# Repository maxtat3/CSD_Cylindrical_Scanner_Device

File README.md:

# Cylindrical Scanner Device (CSD)
This electronic-mechanical device for research of processes in the activation of surfaces by diffusion welding and soldering cylinder samples in a vacuum. It is used for scientific research.
Named: Cylindrical Scanner Device (CSD) or Surface Activation Scanner (SAC) .
You can [view photo](https://drive.google.com/folderview?id=0B9YGrJoTVMatWHJlU2hkQTU4MW8&usp=sharing) when debug this device.

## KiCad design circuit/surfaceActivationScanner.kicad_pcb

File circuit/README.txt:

Project name: 
определение осаждения окиси хрома в вакууме
determining the deposition of chromium oxide in vacuum

This project create in old stable kicad version jul 2013.

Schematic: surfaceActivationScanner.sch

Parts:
C1: 100uF 16V; CP_EIA-7343-31_Kemet-D
C2: 470uF 16V; CP_Elec_10x10
C3: 100uF 6.3V; CP_EIA-3528-21_Kemet-B
C4, C5, C6, C7, C8, C10, C11, C12, C15, C16, C19, C21, C23: 100nF; C_0805_2012Metric
C9, C13, C14: 10uF 16V; CP_EIA-3528-21_Kemet-B
C17, C18: 22pF; C_0805_2012Metric
C20: 1uF; C_1210_3225Metric
C22: 22uF 6.3V; CP_EIA-3528-21_Kemet-B
D1: 10MQ040N; D_SMA
D2: Power; LED_0805_2012Metric
D3: LL4148; D_MiniMELF
D4: FT232_TX_LED; LED_0805_2012Metric
D5: FT232_RX_LED; LED_0805_2012Metric
J1: Conn_power; JST_EH_B02B-EH-A_1x02_P2.50mm_Vertical
J2: Conn_sensor_led; JST_EH_B02B-EH-A_1x02_P2.50mm_Vertical
J3: Conn_opto_int; JST_EH_B03B-EH-A_1x03_P2.50mm_Vertical
J4: Conn_sensor_VT; JST_EH_B02B-EH-A_1x02_P2.50mm_Vertical
J5: Conn btn start/stop msr; JST_EH_B02B-EH-A_1x02_P2.50mm_Vertical
J6: Conn led start/stop msr; JST_EH_B02B-EH-A_1x02_P2.50mm_Vertical
J7: Conn_USB; JST_EH_B03B-EH-A_1x03_P2.50mm_Vertical
J8: AVR-ISP-6; IDC-Header_2x03_P2.54mm_Vertical
JP1: select; JST_EH_B03B-EH-A_1x03_P2.50mm_Vertical
JP2: sel ADC; JST_EH_B03B-EH-A_1x03_P2.50mm_Vertical
L1: 100uH; L_Radial_D8.7mm_P5.00mm_Fastron_07HCP
L2, L3: 100uH; L_Vishay_IHLP-1616
R1, R8, R10, R11, R12, R13: 1k; R_0805_2012Metric
R2, R3, R4, R6, R7: 10k; R_0805_2012Metric
R5, R9: 510E; R_0805_2012Metric
RV1: 1k; Potentiometer_Vishay_T7-YA_Single_Vertical
RV2, RV3: 1k; Potentiometer_Bourns_3296W_Vertical
RV4: 33k; Potentiometer_Bourns_3296W_Vertical
U1: AP1117-50; SOT-223-3_TabPin2
U2: MCP3421A0T-ECH; SOT-23-6_Handsoldering
U3: ATmega8-16AU; TQFP-32_7x7mm_P0.8mm
U4: LM324; SOIC-14_3.9x8.7mm_P1.27mm
U5: FT232RL; SSOP-28_5.3x10.2mm_P0.65mm
Y1: 7.3728 MHz; Crystal_HC49-U_Vertical

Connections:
+9V: C1.1, C4.1, D1.1, L1.1; also elsewhere on the board
/adc_scl: R4.2, U2.3 (SCL), U3.28 (PC5)
/adc_sda: R3.2, U2.4 (SDA), U3.27 (PC4)
/btnStartStop: J5.1, R7.2, U3.32 (PD2)
/ledStartStop: R9.2, U3.13 (PB1)
/mcu_RX: R10.1, U3.30 (PD0)
/mcu_TX: R11.1, U3.31 (PD1)
/miso: J8.1, U3.16 (PB4)
/mosi: J8.4, U3.15 (PB3)
/optoInt: J3.3, R6.2, U3.12 (PB0)
/sck: J8.3, U3.17 (PB5)
/sensor: JP2.3, U3.23 (PC0)
/smen: U3.1 (PD3); also elsewhere on the board
/smw1: U3.2 (PD4); also elsewhere on the board
/smw2: U3.9 (PD5); also elsewhere on the board
/smw3: U3.10 (PD6); also elsewhere on the board
/smw4: U3.11 (PD7); also elsewhere on the board
/~reset: C11.1, D3.2, J8.5, R2.2, U3.29 (PC6/~RESET)
GND: C1.2, C2.2, C3.2, C4.2, C5.2, C6.2, C7.2, C8.2, C9.2, C10.2, C11.2, C12.2, C13.2, C14.2, C15.2, C16.1, C17.2, C18.2, C19.2, C20.2, C21.2, C22.2, C23.2, D2.1 (A), J1.2, J2.2, J3.2, J5.2, J6.2, J7.3, J8.6, R8.2, RV3.2, RV3.3, U1.1 (GND), U2.2 (Vss), U2.6 (Vin-), U3.3 (GND), U3.5 (GND), U3.21 (AGND), U4.11 (V-), U5.7, U5.18, U5.21, U5.25, U5.26; also elsewhere on the board
unnamed: C2.1, C5.1, L1.2, U1.3 (VI)
unnamed: C12.1, C13.1, L2.1, U3.18 (AVCC)
unnamed: C17.1, U3.7 (PB6/XTAL1), Y1.2
unnamed: C18.1, U3.8 (PB7/XTAL2), Y1.1
unnamed: C19.1, U3.20 (AREF)
unnamed: C20.1, JP1.2, U4.3 (+)
unnamed: C21.1, C22.1, L3.1, U5.4, U5.20
unnamed: C23.1, U5.17
unnamed: D1.2, J1.1
unnamed: D2.2 (K), R1.1
unnamed: D4.1 (A), U5.23
unnamed: D4.2 (K), R12.2
unnamed: D5.1 (A), U5.22
unnamed: D5.2 (K), R13.2
unnamed: J2.1, RV1.1
unnamed: J3.1, R5.1
unnamed: J4.1, JP1.3, RV2.2, RV2.3
unnamed: J4.2, JP1.1, RV3.1
unnamed: J6.1, R9.1
unnamed: J7.1, U5.15
unnamed: J7.2, U5.16
unnamed: JP2.1, U2.1 (Vin+)
unnamed: JP2.2, RV4.2, RV4.3, U4.7
unnamed: R8.1, RV4.1, U4.6 (-)
unnamed: R10.2, U5.1
unnamed: R11.2, U5.5
unnamed: U4.1, U4.2 (-), U4.5 (+)

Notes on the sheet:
mcu_RX_green_led
mcu_TX_orange_led
ft232 TX -> mcu RX
ft232 RX <- mcu TX
Sensor LED current set
100nF вместо 0805 в свойствах артикулы для 0603.
Connected to opto interrupter. This help step motor determine start position. Pinout description: 1 - led vcc power 2 - gnd 3 - out opto transistor signal

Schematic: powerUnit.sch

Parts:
C24, C27, C29, C30: 100nF; C_0805_2012Metric
C25: 470uF 16V; CP_Elec_10x12.5
C26: 68uF 16V; CP_EIA-3528-21_Kemet-B
C28: 22uF 16V; CP_EIA-3528-21_Kemet-B
C31: 220pF; C_0805_2012Metric
D6, D7, D8, D9: US1M; D_SMA
D10: 10MQ040N; D_SMA
L4: 15uH; L_12x12mm_H6mm
M1: Stepper_Motor_unipolar_5pin; JST_EH_B05B-EH-A_1x05_P2.50mm_Vertical
Q1, Q2, Q3, Q4: IRLML0030; SOT-23
R14, R16, R19, R23, R25: 1k; R_0805_2012Metric
R15, R21, R24, R26: 51k; R_0805_2012Metric
R17: 22k; R_0805_2012Metric
R18, R22: 100k; R_0805_2012Metric
R20: 68k; R_0805_2012Metric
RV5: 1k; Potentiometer_Vishay_T7-YA_Single_Vertical
U6: MP1584EN-LF-Z; SOIC-8-1EP_3.9x4.9mm_P1.27mm_EP2.35x2.35mm

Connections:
+9V: C26.1, C27.1, U6.7; also elsewhere on the board
/smen: R16.1; also elsewhere on the board
/smw1: R14.2; also elsewhere on the board
/smw2: R19.2; also elsewhere on the board
/smw3: R23.2; also elsewhere on the board
/smw4: R25.2; also elsewhere on the board
GND: C24.2, C25.2, C26.2, C27.2, C28.2, C29.2, C31.2, D10.2, Q1.2, Q2.2, Q3.2, Q4.2, R15.1, R17.2, R18.2, R21.1, R22.2, R24.1, R26.1, U6.5; also elsewhere on the board
unnamed: C24.1, C25.1, C28.1, C29.1, D6.1, D7.1, D8.1, D9.1, L4.2, M1.1, RV5.3
unnamed: C30.1, U6.8
unnamed: C30.2, D10.1, L4.1, U6.1
unnamed: C31.1, R20.2
unnamed: D6.2, M1.5, Q4.3
unnamed: D7.2, M1.4, Q3.3
unnamed: D8.2, M1.2, Q2.3
unnamed: D9.2, M1.3, Q1.3
unnamed: Q1.1, R14.1, R15.2
unnamed: Q2.1, R19.1, R21.2
unnamed: Q3.1, R23.1, R24.2
unnamed: Q4.1, R25.1, R26.2
unnamed: R16.2, R17.1, U6.2
unnamed: R18.1, U6.6
unnamed: R20.1, U6.3
unnamed: R22.1, RV5.1, RV5.2, U6.4

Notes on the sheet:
R=100k : 1MHz R=200k : 500kHz
100nF вместо 0805 в свойствах артикулы для 0603.

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
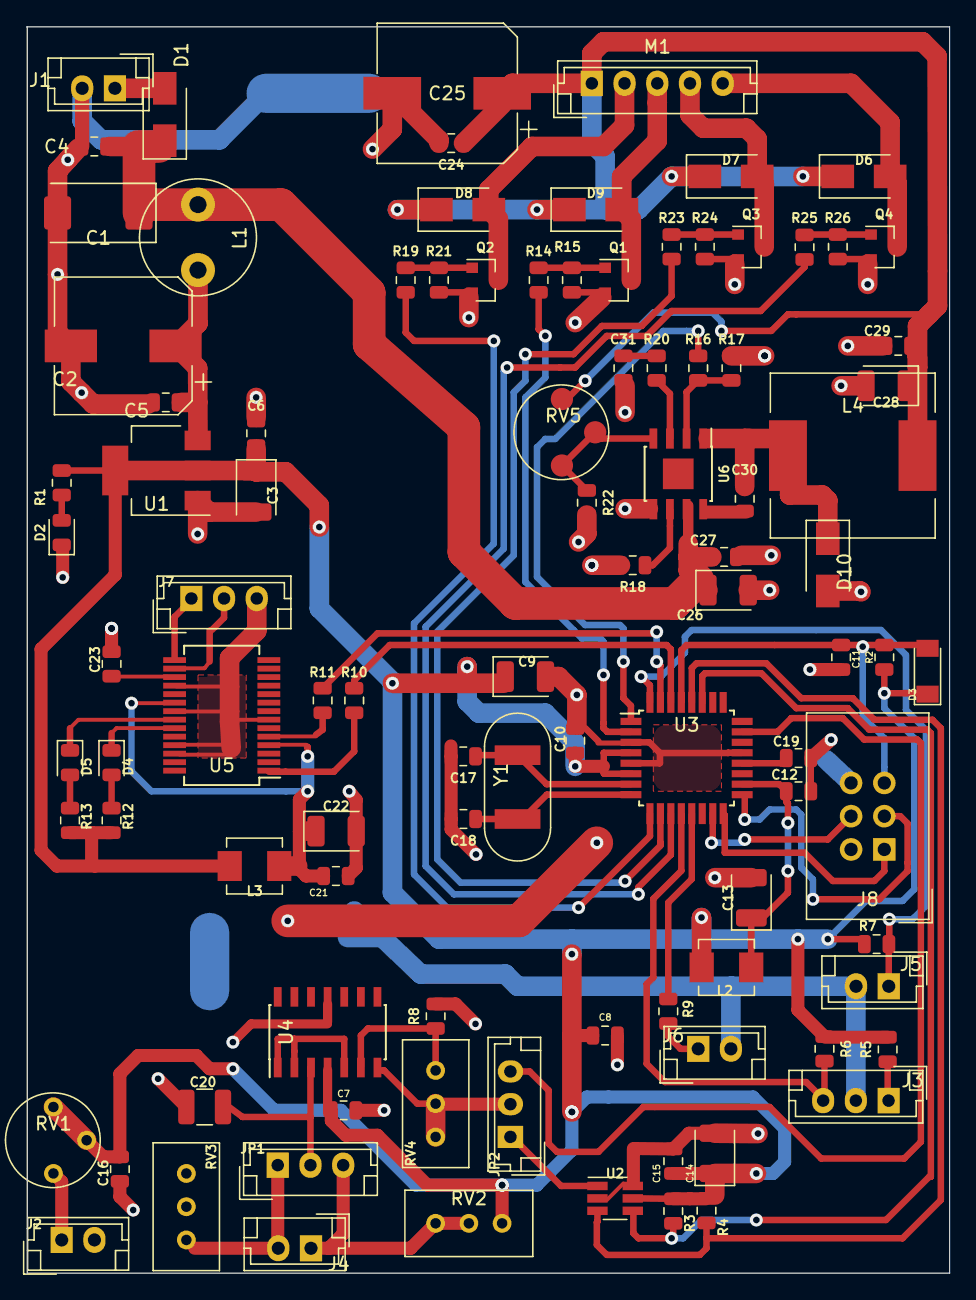
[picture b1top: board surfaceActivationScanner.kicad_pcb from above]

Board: 2 copper layers, 70.5 x 95.3 mm, 98 parts (0 on the bottom side), 63 nets.

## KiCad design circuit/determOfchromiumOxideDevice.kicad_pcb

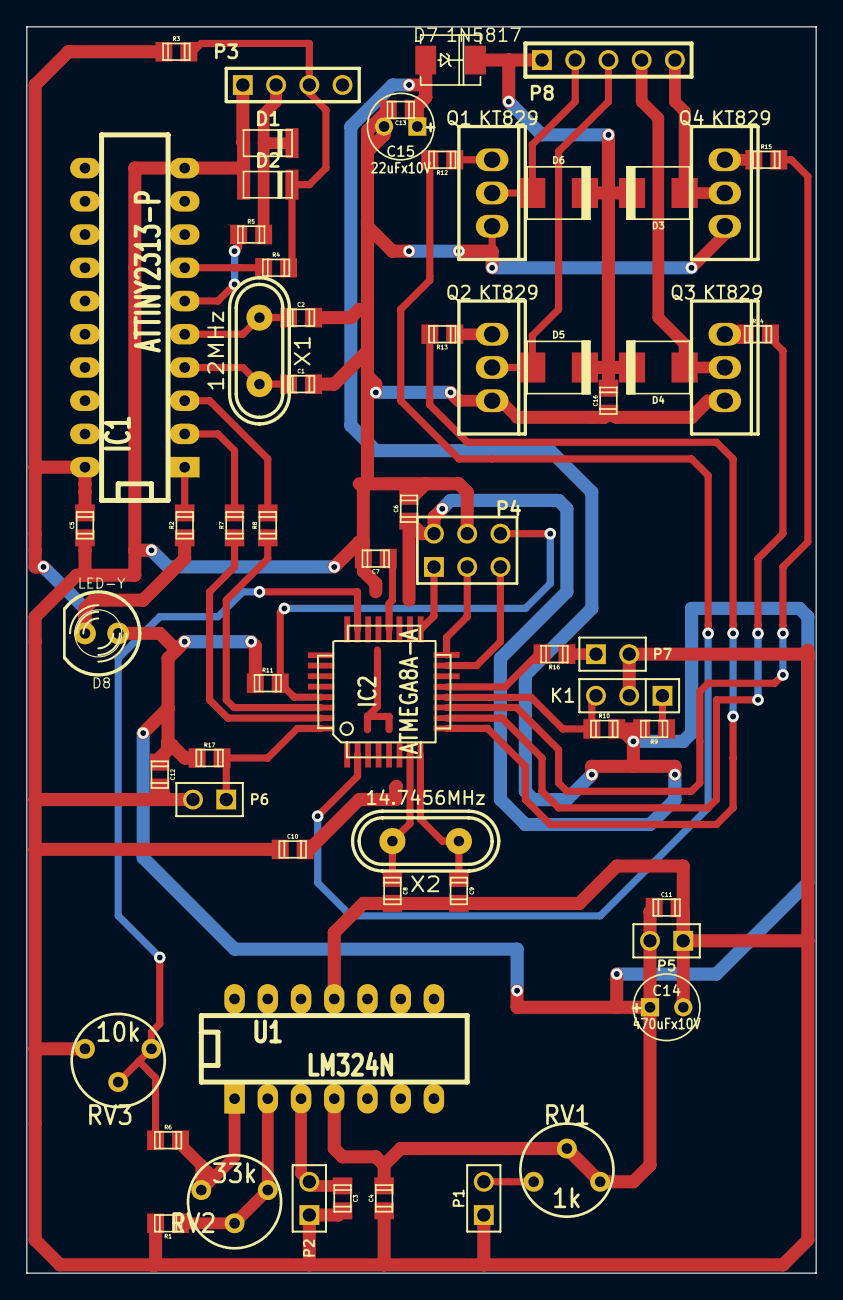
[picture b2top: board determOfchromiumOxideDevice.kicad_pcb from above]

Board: 2 copper layers, 60.3 x 95.2 mm, 62 parts (0 on the bottom side), 44 nets.

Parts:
C1, C2, C8, C9: 22pF; c_0805
C3: 0.01uF; c_0805
C4, C5, C6, C7, C10, C11, C12, C13, C16: 0.1uF; c_0805
C14: 470uFx10V; C1V5
C15: 22uFx10V; C1V5
D1, D2: 3V6; sod87
D3, D4, D5, D6: 1N4007; do214aa
D7: 1N5817; DO-214AC(SMA)
D8: LED-Y; LED-5MM
IC1: ATTINY2313-P; DIP-20__300_ELL
IC2: ATMEGA8A-A; TQFP32
K1: CONN_INPUT_OPTO_INT; PIN_ARRAY_3X1
P1: CONN_SENSOR_LED_POW; PIN_ARRAY_2X1
P2: CONN_SENSOR_SIGNAL_IN; PIN_ARRAY_2X1
P3: CONN_USB; PIN_ARRAY_4x1
P4: CONN_ISP; pin_array_3x2
P5: CONN_POWER; PIN_ARRAY_2X1
P6: CONN_BTN_START_STOP; PIN_ARRAY_2X1
P7: CONN_OUT_IND_PROC_LED; PIN_ARRAY_2X1
P8: CONN_SM; PIN_ARRAY_5x1
Q1, Q2, Q3, Q4: KT829; to220_std
R1: 910; r_0805
R2, R10, R11, R17: 10k; r_0805
R3: 1.5k; r_0805
R4, R5: 68; r_0805
R6: 300; r_0805
R7, R8: 310; r_0805
R9, R12, R13, R14, R15, R16: 510; r_0805
RV1: 1k; RV2
RV2: 33k; RV2
RV3: 10k; RV2
U1: LM324N; DIP-14__300_ELL
X1: 12MHz; crystal_hc-49s
X2: 14.7456MHz; crystal_hc-49s

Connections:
+3.3V: C5.1, D8.2, IC1.20, R2.2, R3.2
/RX: IC2.31, R7.2
/TX: IC2.30, R8.2
/USB_D+: IC1.6, R5.2
/USB_D-: IC1.7, R4.2
/btnStartStop: IC2.32, P6.1, R17.1
/indProcLed: IC2.13, R16.1
/miso: IC2.16, P4.3
/mosi: IC2.15, P4.5
/optoIntIn: IC2.12, K1.3, R10.2
/res: IC2.29, P4.6, R11.1
/sck: IC2.17, P4.1
/sensorSignalIn: IC2.23, R6.2, RV3.1, RV3.2
/smWire1: IC2.2, R12.1
/smWire2: IC2.9, R13.1
/smWire3: IC2.10, R14.1
/smWire4: IC2.11, R15.1
GND: C1.1, C2.1, C3.1, C4.2, C5.2, C6.1, C7.1, C8.1, C9.1, C10.2, C11.1, C12.1, C13.1, C14.2, C15.2, C16.2, D1.1, D2.1, IC1.10, IC2.3, IC2.5, IC2.21, K1.2, P1.1, P2.1, P3.1, P4.4, P5.1, P6.2, P7.2, Q1.1, Q2.1, Q3.1, Q4.1, R1.1, RV3.3, U1.11
unnamed: R1.2, RV2.1, RV2.2, U1.2
unnamed: D5.1, P8.3, Q2.2
unnamed: D6.1, P8.2, Q1.2
unnamed: D3.1, P8.5, Q4.2
unnamed: D4.1, P8.4, Q3.2
unnamed: C7.2, IC2.20
unnamed: C8.2, IC2.7, X2.2
unnamed: C9.2, IC2.8, X2.1
unnamed: IC1.2, R7.1
unnamed: D1.2, P3.2, R5.1
unnamed: D2.2, P3.3, R3.1, R4.1
unnamed: Q4.3, R15.2
unnamed: Q3.3, R14.2
unnamed: Q2.3, R13.2
unnamed: P7.1, R16.2
unnamed: C3.2, P2.2, U1.3
unnamed: R6.1, RV2.3, U1.1
unnamed: Q1.3, R12.2
unnamed: P1.2, RV1.1
unnamed: IC1.3, R8.1
unnamed: IC1.1, R2.1
unnamed: K1.1, R9.2
unnamed: C1.2, IC1.4, X1.2
unnamed: C2.2, IC1.5, X1.1
VAA: C16.1, D3.2, D4.2, D5.2, D6.2, D7.2, P8.1
VCC: C4.1, C6.2, C10.1, C11.2, C12.2, C13.2, C14.1, C15.1, D7.1, D8.1, IC2.4, IC2.6, IC2.18, P4.2, P5.2, R9.1, R10.1, R11.2, R17.2, RV1.2, RV1.3, U1.4

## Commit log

2015-12-10 Рабочий вариант прошивки v 1.0
2015-12-10 ДОбавлен пустой проект для пк
2015-12-10 Update project files
2015-12-10 rm files
2015-12-10 Update jdk version in gradle props
2015-12-10 Add gradle config add main application class.
2015-12-10 Add chart container
2015-12-10 Resolved BUG which does not establish a connection after re-initialization of the new com port! Modified chart color scshema.
2015-12-10 Modified gitignore. Add kicad circuit part.
2015-12-10 На схеме: добавлено описание какой Ку нужно установить, изменены номиналы R для ОУ, изменен номинал С3. Исправлена ошибка монтажа - были перепутаны usb data которые идут на tn2313, D+ был не туда под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
2015-12-10 Modified circuit and export to png.
2015-12-10 Create empty info folder for support documentation.
2015-12-10 Add information help file. Add to gitignore info files
2015-12-12 Change main class in gradle for create jar.
2015-12-12 Change .gitignore - forbid add /build folder to repo.
2015-12-12 Выполнен полный рефакторинг.
2015-12-14 Add meander generator, for testing received data and change uniformity time intervals in chart in jse app
2015-12-14 Рефакторинг jse кода.
2015-12-14 Убраны не используемые ui компоненты: кнопка clear и textarea.
2015-12-14 Изменено кол-во точек графика ф-ии одновременно выводимых на одном экране.
2015-12-14 ДОбавлен простой функционал для записи полученных резульататов измерения в файл с именем даты и время. В файл пишуться только значения ацп. Запись происходит только когда после запуска процесса польз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
2015-12-14 Убраны неиспользуемый код. Предназначался для тестирования отправки строки в приложение перед началом запуска измерений.
2015-12-14 Update gitignore - add csv files.
2015-12-14 В приложение и mcu добавлен механизм иденитификации устройства. Если ком порт открыт то выполнеться попытка установления связи между приложением и устройством. Приложение инициирует сеанс идентификац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
2015-12-15 В этом коммите добавлен функционал для автоматического определения com порта устройства. Если com порт найден - выполняеться подключение, если нет - com порт остаеться по умол. - com1. И соответствен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
2015-12-15 Если при автоопределении не удалось обнаружить устройство - выводиться информационное сообщение в модальном окне. Также добавлен вывод модального окна при ручном выборе ком порта.
2015-12-15 Увеличена скорость вращения ШД в обратном направлении.
2015-12-15 Перед стартом каждого нового измерения стираеться предыдущий график.
2015-12-15 Рефакторинг обработчика запуска и остановки измерений.
2015-12-16 В этом коммите ИСПРАВЛЕНА случайно стертая строка вызова метода записи в файл. Это исправление касаеться предыдущего комита. НО запись в файл тут работает только при нажатии на кнопку Стоп.
2015-12-16 Этот коммит вводит синхронизацию между количеством шагов и еденицами измерения длины образца в мм. Значения ацп передаються в приложение каждые 0.2 мм при перемещении каретки (червяка). Это позволяет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
2015-12-16 При сохранеиии в файл добавляються такие данные в столбцах: номер точки, значения длины образца, напряжение в 8 битной сетке .
2015-12-16 Изменено условие инициализации ком порта для лучшей читаемости.
2015-12-16 Рефакторинг. Переименнованы некоторые переменные, добавлены комментарии, немного изменен код в обработчике кнопки СтартСтоп.
2015-12-16 Метод deviceComPortAutoConnect перенесен в класс UART. Добавлен сброс всех переменных отвечающих за процесс записи при старте нового измерения образца.
2015-12-16 Функционал для записи результатов в файл перенесен в новый класс.
2015-12-16 В названиях подписей к столбцам при сохранении в файл запятые изменены на скобки т.к. например в libreoffice calc запятые являються разделителями включенными по умолчанию.
2015-12-16 Добавлена возможность изменения масштаба по оси Y .
2015-12-17 Добавлены подписи к осям x и y . Цвета примененные на графике вынесены в константы.
2015-12-17 Уменьшено количество буфера для отображения точек на экране и при записи. Изменены параметры сигнатуры класса для записи данных в файл.
2015-12-17 Убран код NumberFormat. При этом между написью оси y и самой осью появилось свободное место. До этого надпись почти сливалась с осью.
2015-12-17 ДОбавлены комментарии к неподписанным методам.
2015-12-18 Изменение протокола передачиданных между устройством и пприложением. Промежуточный вариант. На стороне мк переписаниы ф-ии отправки данных. Добавлены дополнительные комментарии к ф-ии ининициализации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
2016-03-09 Изменен регистр константы RESPONSE_INIT_DEVICE для отправки команд в приложение. Команды и данные теперь отправляются в прерывании таймера 0. Это нужно для асинхронной передайчи байт на ПК в приложен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
2016-04-04 Updated documentation. Added all main sections.
2016-04-04 Updated documentation.
2016-04-04 Updated doc - pre relase.
2016-09-07 New version of documentation.
2016-09-07 Add short user manual.
2016-09-07 Additional materials.
2018-10-19 Changed input photo signal part in schematic - added RV and emitter repeater cascade in LM324. Changed amp gain.Important - input part in LM324 in schematic do not match from PCB layout.
2018-10-19 Added schematic png file from prev commit.
2018-10-19 Added image opto-interrupter image, renamed some files in etc dir.
2018-10-19 Renamed mcu dir to firmware.
2018-10-19 Redesign schematic - input amp, interface in FT232, step motor driver in MOSFET-s. Full repaint schematic in KiCAD 5.
2018-10-19 Added schematic png images.
2018-10-20 Fix bug in schematic - added connection SM enable from DC-DC convertor to MCU.
2018-10-25 In powerUnit.sch changed 15uHn to 15uH.
2018-10-25 Performed tracing PCB: dimmednsions 95 x 70 mm, double sided board.
2018-10-25 Added gradient lines for test sensor.
2018-11-28 Added articles for some components in powerUnit schematic.
2018-11-28 Added articles for some components in main schematic.
2018-11-28 Changed gitignore file - expand KiCad ignore files. Added delimiters between sections.
2018-11-29 Firmware. Added support power supply for step motor (SM). Changed programmer and port in Makefile.
2018-11-29 Firmware. Refactoring.
    Moved setbit, clearbit,... macroses to single module.
2018-11-29 Firmware. Refactoring. Changed all full types to short.
2018-11-29 Firmware. Refactoring. Moved uart part to single module.
2018-11-29 Firmware. Refactoring. Moved adc part to single module.
2018-11-30 Firmware. Remove not used blinkled funct-s. Make process led indication.
2018-11-30 Firmware. Tiny Refactoring indication module.
2018-12-10 Firmware. Refactoring. Opto interrupter handler move to single module. Added blink led support when caret is parking to home position.
2018-12-10 Firmware. Refactoring. Removed not used timer2 handler for generate meander.
2018-12-12 Added CH340 interface module driver
2018-12-12 App. For UI direction elements increased text size and translated to russian.
2018-12-12 App. Added horizontal spaces from directions UI elements in top panel. Added tooltip text for COM port. Improved COM ports list.
2018-12-12 App. Improved. Added orange color background checkbox highlight when record is selected.
2018-12-12 App. Fix to prev commit.
2018-12-13 App. Improved. Add hot keys (mnemonic).
2018-12-13 App. Improved tooltips.
2018-12-13 App. Improved. Moved constants to groups
    In this commit do not modify any constants, only moved by groups. fo
2018-12-13 App. Improved. General font moved to constants.
2018-12-13 App. Set window title text.
2018-12-13 App. Changes Y axis and their minor and major interval.
    In Y axis change max value to 100 percents. And change label name.
2018-12-13 Firmware. Fix. Changed adc sync coefficient.
    This coeff determined number of steps to skip before sending the ADC
    value from the light sensor.
    In this coeff tested - sending ~300 adc values from 60 mm length of
    sample. In chart in full length of sample can view 60 mm in X axis.
    See issue #32 .
2018-12-13 App. Maked generate versioning jar.
2019-01-24 Firmware. Fix. Sometimes not responsed mcu to app in init process. This chnages does not affect anything. Button start-stop in device(server) do not work.
2019-01-25 App. Firmware. Full rewrite translate and response (request and response) part. Changed from sending alternately single Bytes command and data to package sending.
2019-01-28 App. Firmware. In app make block UI elements when mechanical system make parking in start position.
2019-01-28 App. Refactoring. Renamed callback interface for GUI.
2019-01-28 App. Displaying server status in label.
